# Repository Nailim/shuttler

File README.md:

# shuttler
Code dump for project shuttler - https://scientiatertiidimension.blogspot.com

What was project shuttler?

A project to build a mapping drone for 3D terain reconstruction which included an autopilot build for Android phones, 360° video processing, image processing, 3D pritnting, electronics design and all other neceseties when building a drone from scratch.

More info on the project blog.

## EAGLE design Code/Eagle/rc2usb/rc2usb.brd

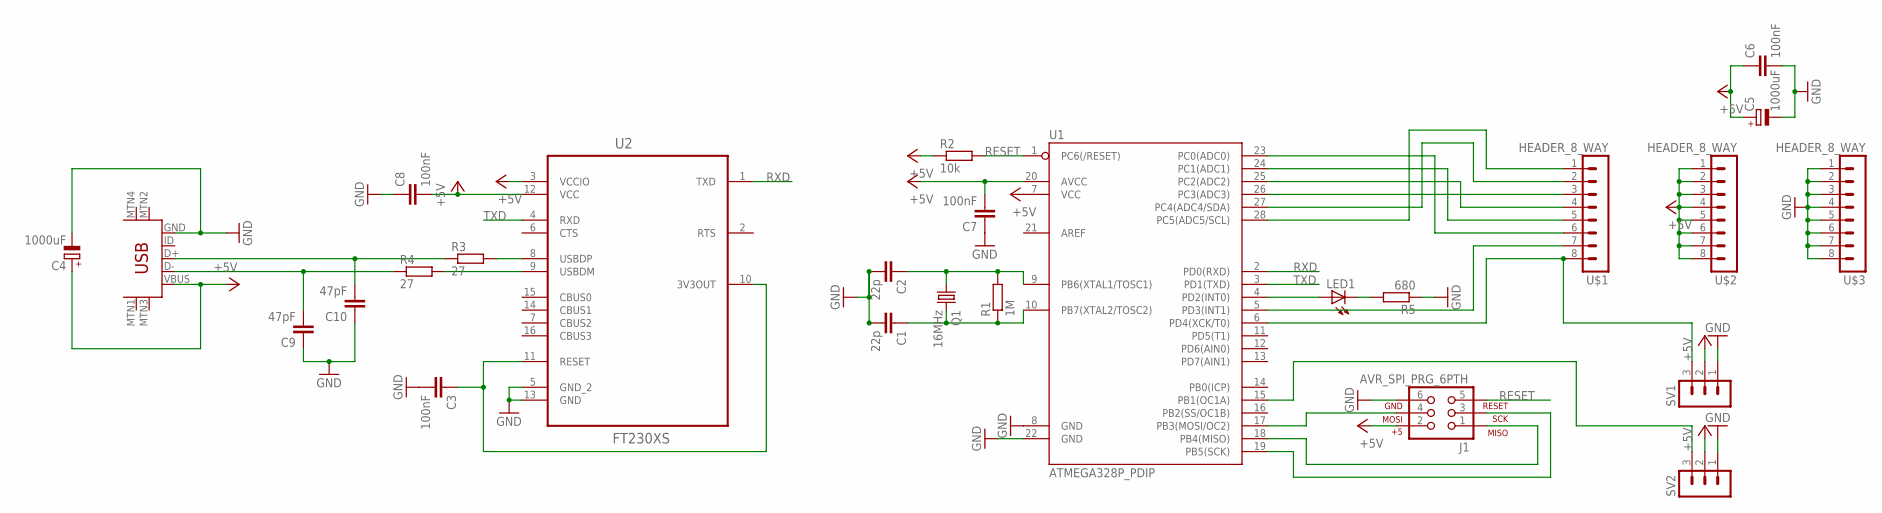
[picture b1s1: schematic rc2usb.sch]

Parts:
C1, C2: 22p; C025-040X050
C3, C6, C7, C8: 100nF; C025-030X050
C4, C5: 1000uF; E5-10,5
C9, C10: 47pF; C025-030X050
J1: AVR_SPI_PRG_6PTH; 2X3
LED1: LED5MM
Q1: 16MHz; HC49U70
R1: 1M; 0207/10
R2: 10k; 0207/10
R3, R4: 27; 0207/10
R5: 680; 0207/10
SV1, SV2: MA03-1
U1: ATMEGA328P_PDIP; DIL28-3
U2: FT230XS; SOP63P600X175-16N
U$1, U$2, U$3: HEADER_8_WAY
U$4: USB-MINIB-5PIN; USB-MINIB

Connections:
+5V: C4.+, C5.+, C6.1, C7.2, C8.2, J1.2, R2.1, SV1.2, SV2.2, U1.7 (VCC), U1.20 (AVCC), U2.3 (VCCIO), U2.12 (VCC), U$2.1, U$2.2, U$2.3, U$2.4, U$2.5, U$2.6, U$2.7, U$2.8, U$4.VBUS
GND: C1.2, C2.2, C3.2, C4.-, C5.-, C6.2, C7.1, C8.1, C9.1, C10.1, J1.6, R5.1, SV1.1, SV2.1, U1.8 (GND), U1.22 (GND), U2.5 (GND_2), U2.13 (GND), U$3.1, U$3.2, U$3.3, U$3.4, U$3.5, U$3.6, U$3.7, U$3.8, U$4.GND
unnamed: C2.1, Q1.1, R1.2, U1.9 (PB6(XTAL1/TOSC1))
unnamed: C1.1, Q1.2, R1.1, U1.10 (PB7(XTAL2/TOSC2))
unnamed: J1.4, U1.17 (PB3(MOSI/OC2))
unnamed: J1.1, U1.18 (PB4(MISO))
unnamed: J1.3, U1.19 (PB5(SCK))
unnamed: C10.2, R3.1, U$4.D+
unnamed: C9.2, R4.1, U$4.D-
unnamed: U1.24 (PC1(ADC1)), U$1.5
unnamed: R3.2, U2.8 (USBDP)
unnamed: LED1.A, U1.4 (PD2(INT0))
unnamed: C3.1, U2.10 (3V3OUT), U2.11 (RESET)
unnamed: R4.2, U2.9 (USBDM)
unnamed: U1.25 (PC2(ADC2)), U$1.4
unnamed: U1.26 (PC3(ADC3)), U$1.3
unnamed: U1.23 (PC0(ADC0)), U$1.6
unnamed: U1.27 (PC4(ADC4/SDA)), U$1.2
unnamed: U1.28 (PC5(ADC5/SCL)), U$1.1
unnamed: U1.5 (PD3(INT1)), U$1.7
unnamed: SV1.3, U1.6 (PD4(XCK/T0)), U$1.8
unnamed: SV2.3, U1.15 (PB1(OC1A))
unnamed: LED1.K (C), R5.2
RESET: J1.5, R2.2, U1.1 (PC6(/RESET))
RXD: U1.2 (PD0(RXD)), U2.1 (TXD)
TXD: U1.3 (PD1(TXD)), U2.4 (RXD)

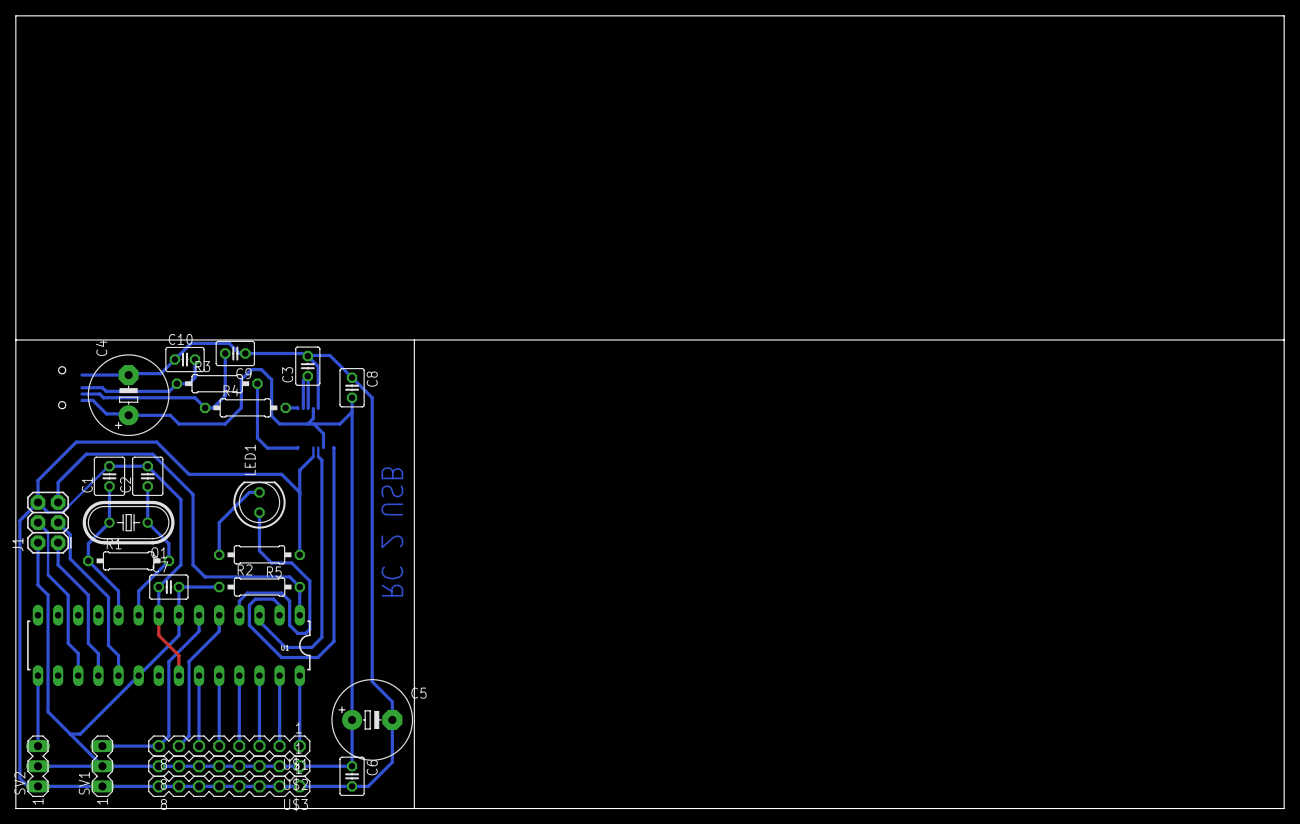
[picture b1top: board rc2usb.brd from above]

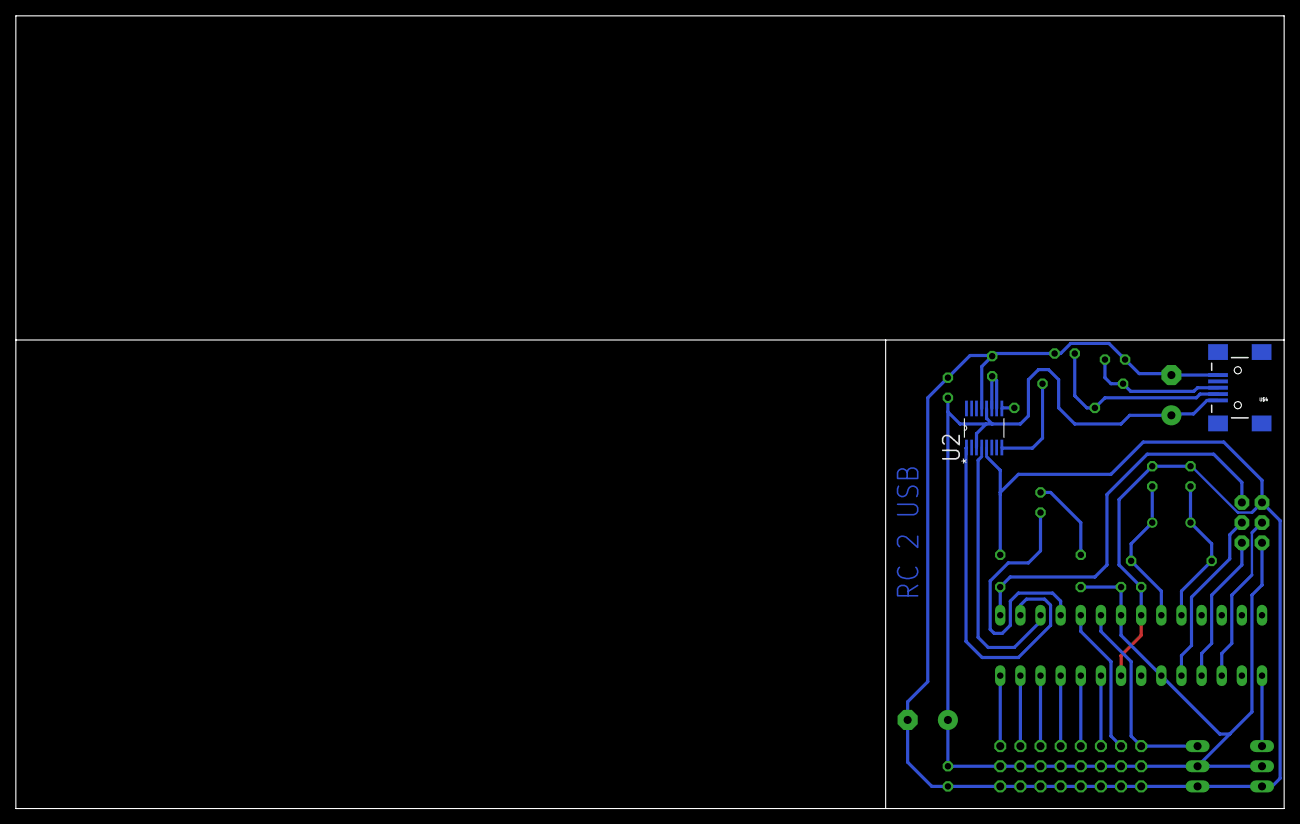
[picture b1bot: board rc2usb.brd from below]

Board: 2 copper layers, 160.0 x 100.0 mm, 26 parts (2 on the bottom side), 26 nets.

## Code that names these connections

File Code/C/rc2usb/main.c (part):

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#define MYUBRR FOSC/16/BAUD-1

// global variables
volatile unsigned char port_c_last = 0x00;		// pin change interrupts PC0-5
volatile unsigned char port_c_change = 0x00;	// pin change interrupts PC0-5
volatile unsigned char port_d_last = 0x00;		// pin change interrupts PD3-4
volatile unsigned char port_d_change = 0x00;	// pin change interrupts PD3-4

volatile unsigned short timer_temp = 0x0000;
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	port_d_last = (PIND & PCMSK2);
	
	// find and service the apropriate pins
	if (port_c_change & 0x20) {			// channel 1 (PC5 - PCINT 13 - PCMSK1 bit 5)
		if (port_c_last & 0x20) {		// low to hight
			timer_temp_storage[0] = timer_temp;
		}
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			}
		}
	}
	if (port_c_change & 0x10) {			// channel 2 (PC4 - PCINT 12 - PCMSK1 bit 4)
		if (port_c_last & 0x10) {		// low to hight
			timer_temp_storage[1] = timer_temp;
		}
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			}
		}
	}
	if (port_c_change & 0x08) {			// channel 3 (PC3 - PCINT 11 - PCMSK1 bit 3)
		if (port_c_last & 0x08) {		// low to hight
			timer_temp_storage[2] = timer_temp;
		}
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			}
		}
	}
	if (port_c_change & 0x04) {			// channel 4 (PC2 - PCINT 10 - PCMSK1 bit 2)
		if (port_c_last & 0x04) {		// low to hight
			timer_temp_storage[3] = timer_temp;
		}
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			}
		}
	}
	if (port_c_change & 0x02) {			// channel 5 (PC1 - PCINT 9 - PCMSK1 bit 1)
		if (port_c_last & 0x02) {		// low to hight
			timer_temp_storage[4] = timer_temp;
		}
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			}
		}
	}
	if (port_c_change & 0x01) {			// channel 6 (PC0 - PCINT 8 - PCMSK1 bit 0)
		if (port_c_last & 0x01) {		// low to hight
			timer_temp_storage[5] = timer_temp;
		}
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			}
		}
	}
	if (port_d_change & 0x08) {			// channel 7 (PD3 - PCINT 19 - PCMSK2 bit 3)
		if (port_d_last & 0x08) {		// low to hight
			timer_temp_storage[6] = timer_temp;
		}
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			}
		}
	}
	if (port_d_change & 0x10) {			// channel 8 (PD4 - PCINT 20 - PCMSK2 bit 4)
		if (port_d_last & 0x10) {		// low to hight
			timer_temp_storage[7] = timer_temp;
		}
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}

int main(void) {
	// set PD2 as output - LED
	DDRD |= 0x04;
	PORTD &= ~0x04;		// LED (PD2) off
	
	// set PB1 as output - PWM
	DDRB |= 0x02;
	
	// set PC0-5 (PCI1) & PD3-4 (PCI2) as input - PIN CHANGE INTERRUPT
	DDRC &= ~0x3F;
	DDRD &= ~0x19;	// includes the RX to FT230X
	
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	OCR1B = 49999;						// set Output Compare Register for 50Hz (once every 20ms)
	
	// set PIN CHANGE INTERRUPT
	PCICR |= 1<<PCIE1 | 1<<PCIE2;		// enable pin change interrupts PC0-5 (PCI1) & PD3-4 (PCI2)
	PCMSK1 |= 1<<PCINT13 | 1<<PCINT12 | 1<<PCINT11 | 1<<PCINT10 | 1<<PCINT9 | 1<<PCINT8;	// enable pins PC0-5 (PCI1)
	PCMSK2 |= 1<<PCINT20 | 1<<PCINT19;														// enable pins PD3-4 (PCI2)
	
	// enable interrups
	sei();	
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
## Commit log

2017-11-05 Add project source sode.
2017-11-05 Add required directory for image processing.
2017-11-05 Add required directory for autopilot telemetry processing with example.
2017-11-05 Add workflow scripts.

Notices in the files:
parts and their libraries:
SparkFun-DigitalIC: Licensing: CC v3.0 Share-Alike You are welcome to use this library for commercial purposes.
